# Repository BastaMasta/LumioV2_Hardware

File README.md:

# Lumio V2 Hardware

A repo containing all the hardware (shematic and PCB) files for the Lumio V2 Main Board

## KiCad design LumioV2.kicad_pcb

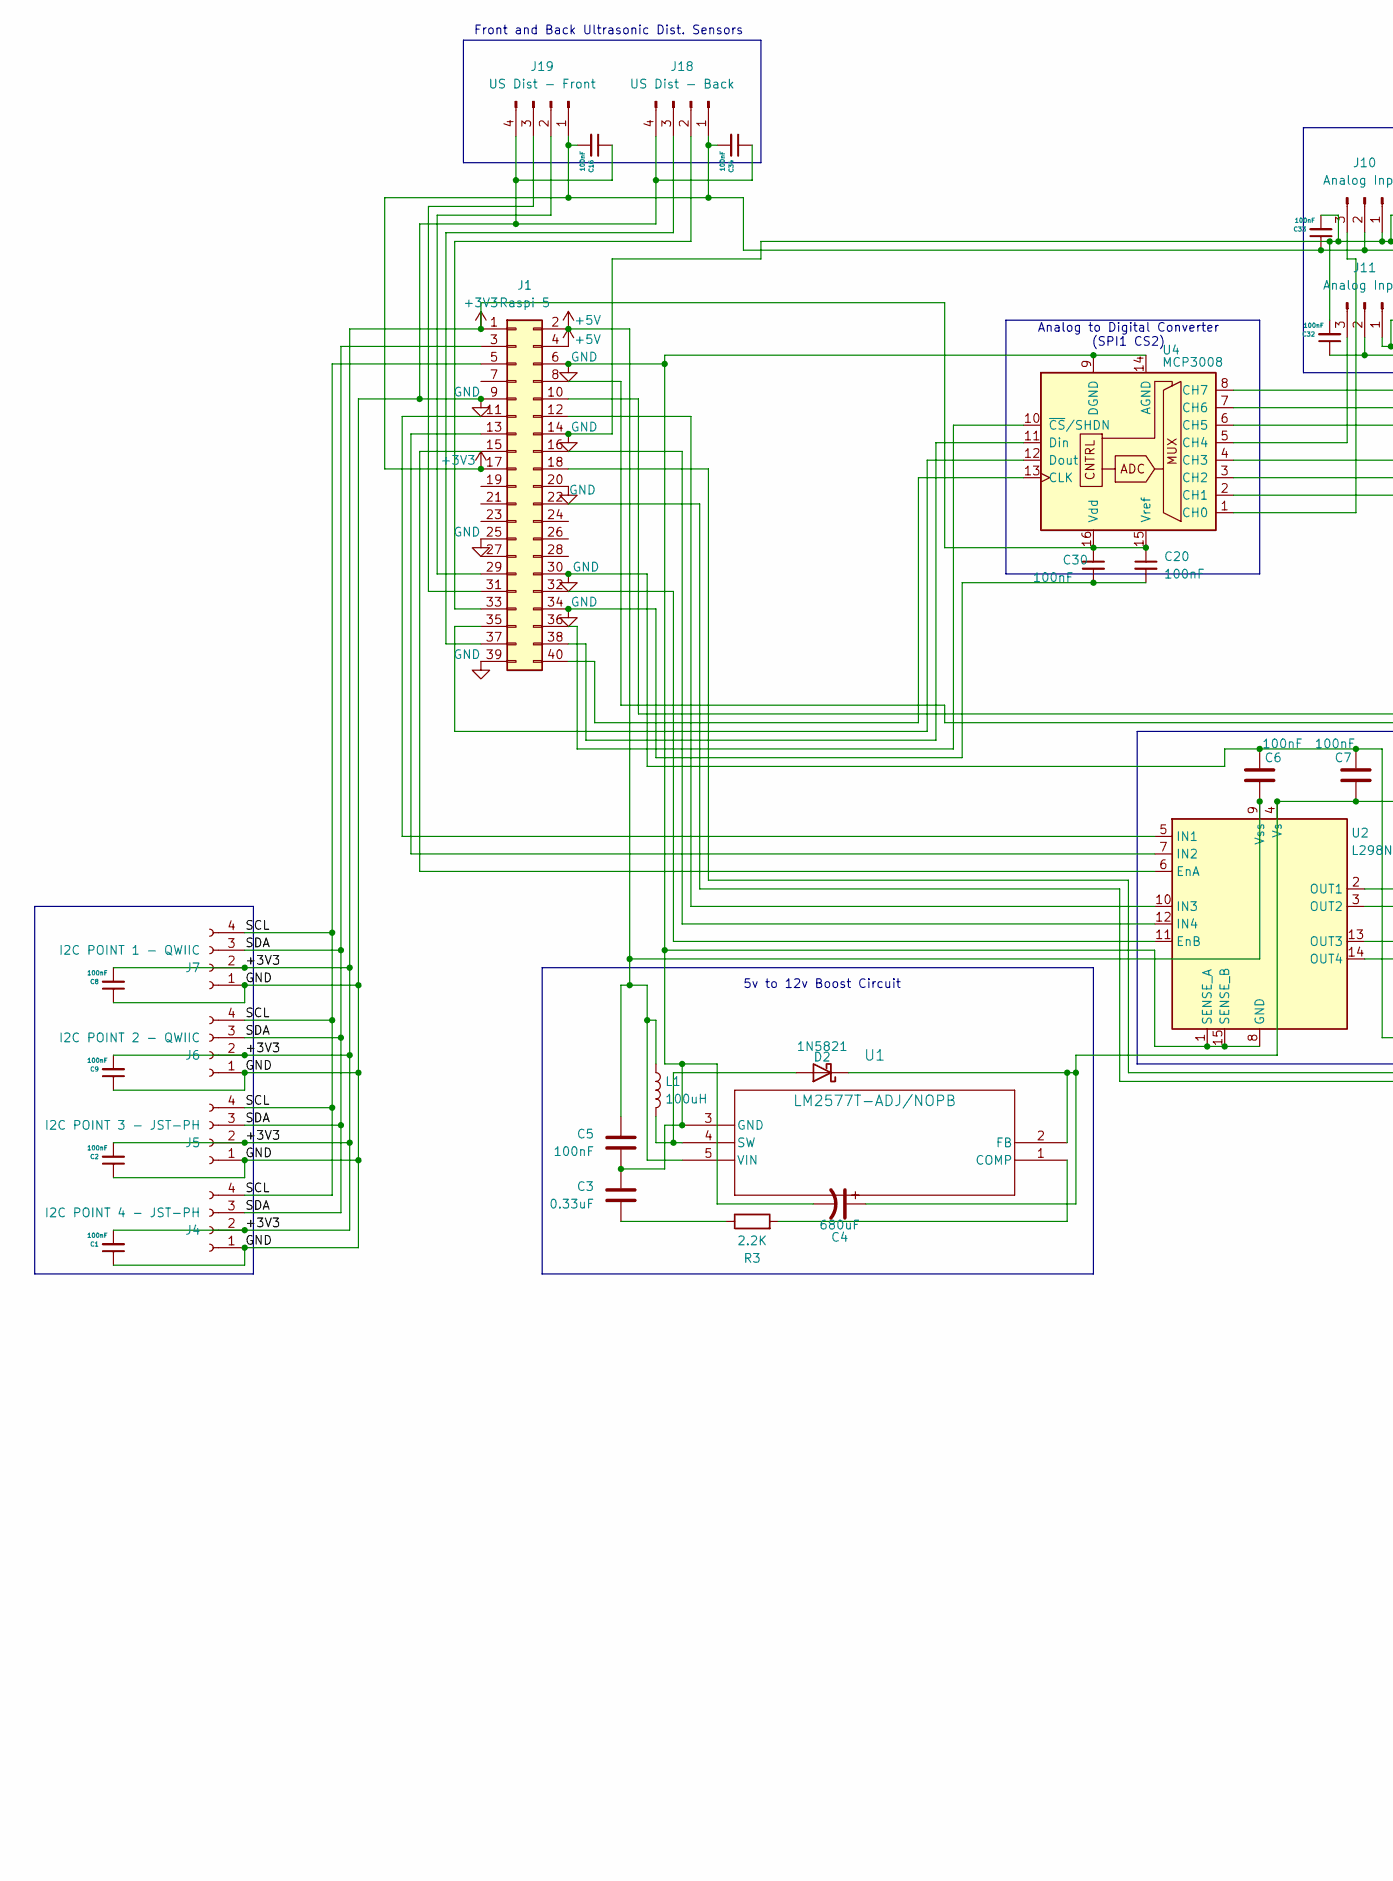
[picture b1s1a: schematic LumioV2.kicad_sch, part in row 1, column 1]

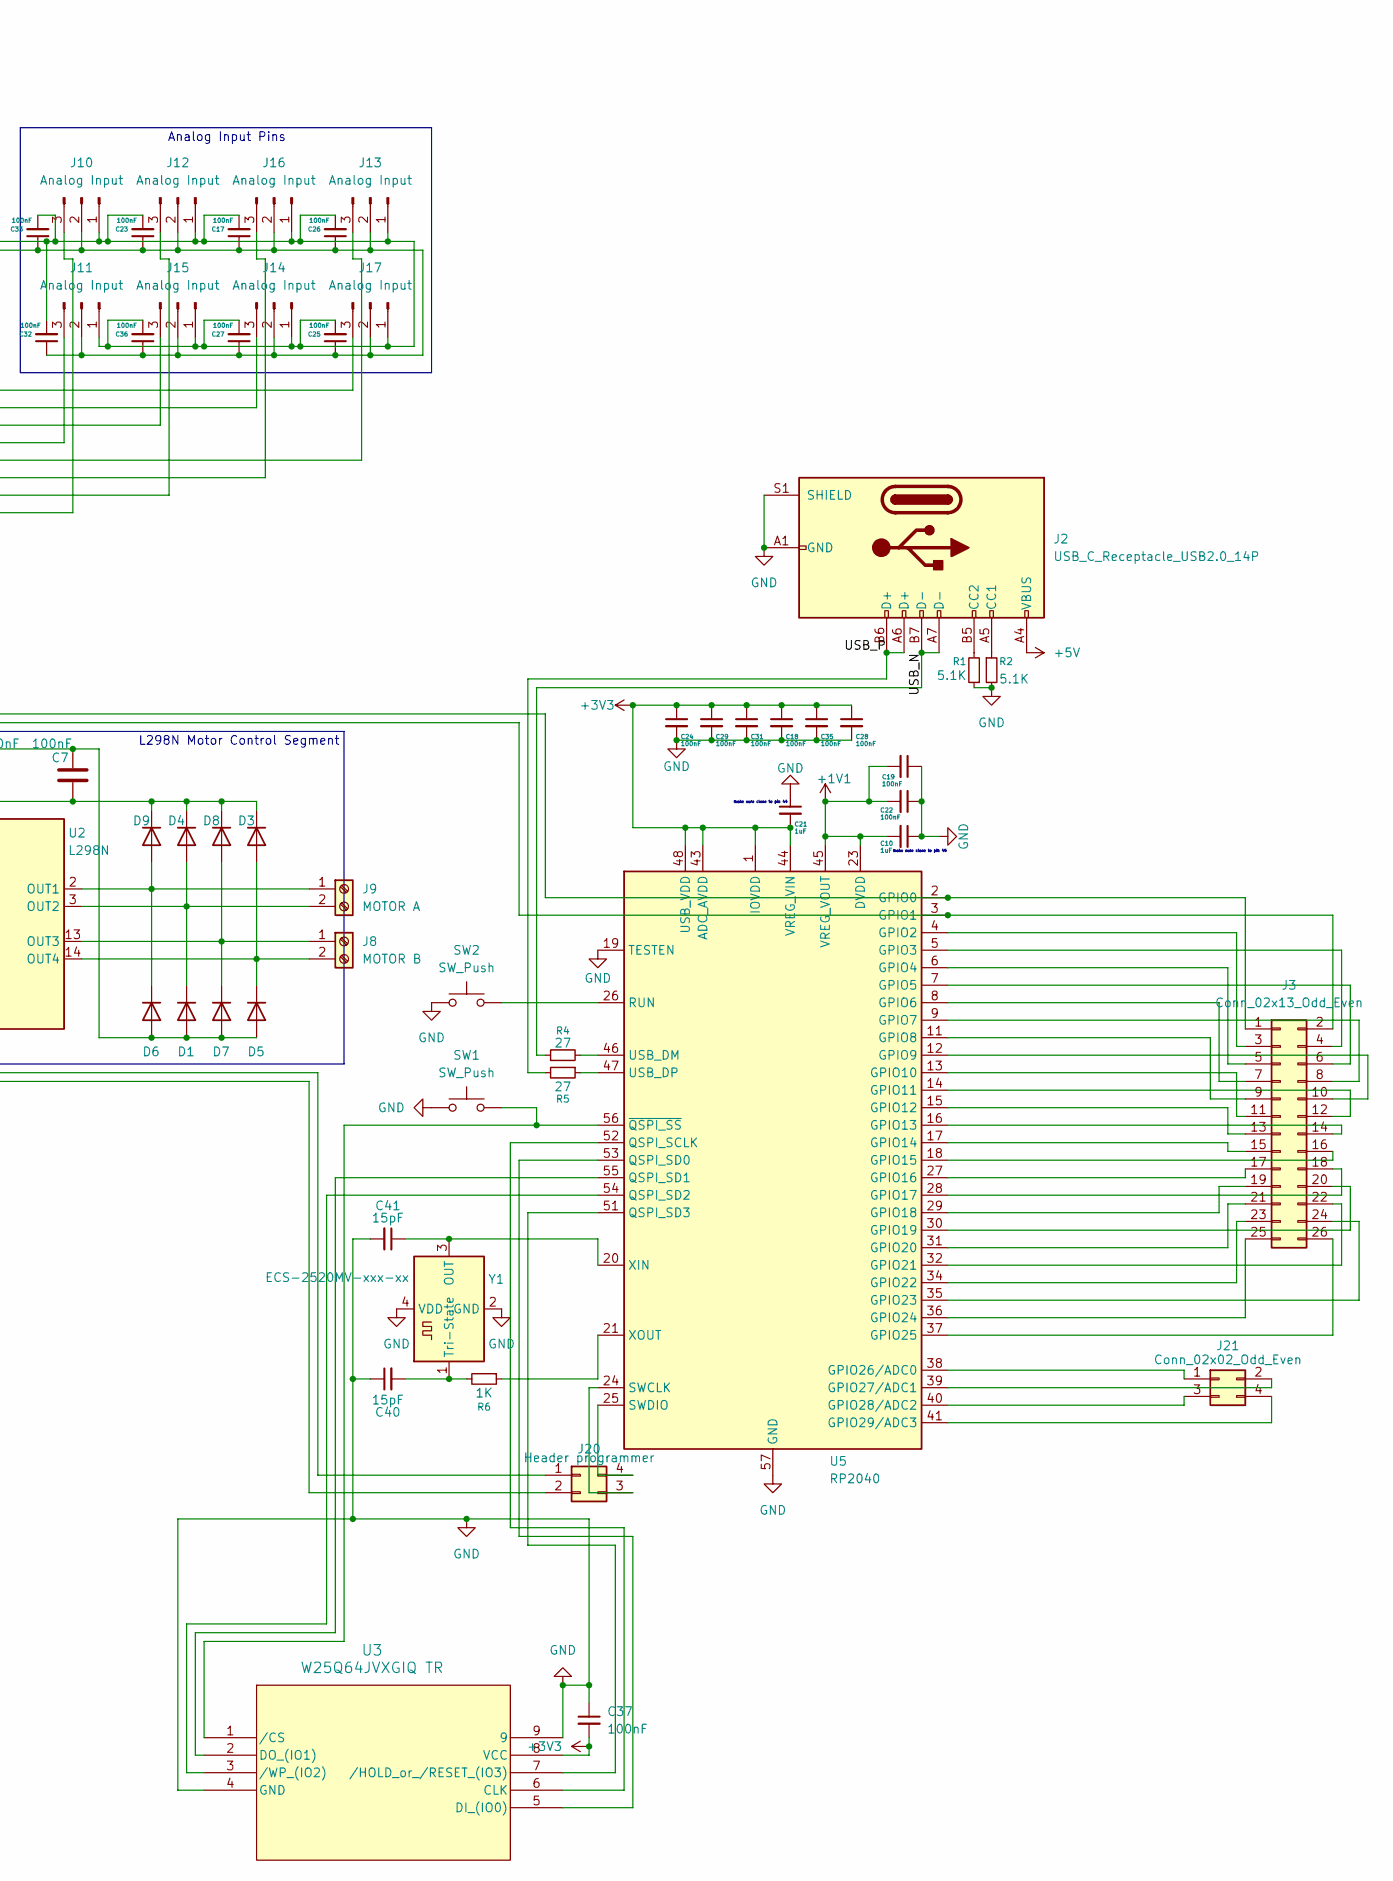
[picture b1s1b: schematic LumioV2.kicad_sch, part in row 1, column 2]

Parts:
C1, C2, C5, C6, C8, C9, C16, C17, C18, C19, C20, C22, C23, C24, C25, C26, C27, C28, C29, C30, C31, C32, C33, C34, C35, C36, C37: 100nF; C_0402_1005Metric_Pad0.74x0.62mm_HandSolder
C3: 0.33uF; C_0402_1005Metric_Pad0.74x0.62mm_HandSolder
C4: 680uF; CP_Elec_10x10
C7: 100nF; C_1210_3225Metric
C10, C21: 1uF; C_0402_1005Metric_Pad0.74x0.62mm_HandSolder
C40, C41: 15pF; C_0402_1005Metric_Pad0.74x0.62mm_HandSolder
D1, D3, D4, D5, D6, D7, D8, D9: SS34B; D_SMA_Handsoldering
D2: 1N5821; D_DO-201AD_P15.24mm_Horizontal
J1: Raspi 5; PinHeader_2x20_P2.54mm_Vertical; DIGIKEY ED-PI400EXT-G
J2: USB_C_Receptacle_USB2.0_14P; USB_C_Receptacle_G-Switch_GT-USB-7010ASV
J3: Conn_02x13_Odd_Even; PinHeader_2x13_P2.54mm_Horizontal
J4: I2C POINT 4 - JST-PH; JST_PH_B4B-PH-SM4-TB_1x04-1MP_P2.00mm_Vertical
J5: I2C POINT 3 - JST-PH; JST_PH_B4B-PH-SM4-TB_1x04-1MP_P2.00mm_Vertical
J6: I2C POINT 2 - QWIIC; JST_SH_BM04B-SRSS-TB_1x04-1MP_P1.00mm_Vertical
J7: I2C POINT 1 - QWIIC; JST_SH_BM04B-SRSS-TB_1x04-1MP_P1.00mm_Vertical
J8: MOTOR B; TerminalBlock_MaiXu_MX126-5.0-02P_1x02_P5.00mm
J9: MOTOR A; TerminalBlock_MaiXu_MX126-5.0-02P_1x02_P5.00mm
J10, J11, J12, J13, J14, J15, J16, J17: Analog Input; PinHeader_1x03_P2.54mm_Vertical
J18: US Dist - Back; PinHeader_1x04_P2.54mm_Vertical
J19: US Dist - Front; PinHeader_1x04_P2.54mm_Vertical
J20: Header programmer; PinHeader_2x02_P2.54mm_Vertical
J21: Conn_02x02_Odd_Even; PinHeader_2x02_P2.54mm_Vertical
L1: 100uH; L_Radial_D10.0mm_P5.00mm_Fastron_07M
R1, R2: 5.1K; R_0603_1608Metric
R3: 2.2K; R_0805_2012Metric_Pad1.20x1.40mm_HandSolder
R4, R5: 27; R_0603_1608Metric
R6: 1K; R_0603_1608Metric
SW1, SW2: SW_Push; SW_SPST_PTS647_Sx50
U1: LM2577T-ADJ/NOPB; T05A_TEX
U2: L298N; TO-220-15_P2.54x5.08mm_StaggerOdd_Lead4.58mm_Vertical
U3: W25Q64JVXGIQ TR; DFN-8-1EP_6x5mm_P1.27mm_EP4x4mm
U4: MCP3008; DIP-16_W7.62mm_Socket_LongPads; PART MCP3008-I/SL
U5: RP2040; QFN-56-1EP_7x7mm_P0.4mm_EP3.2x3.2mm
Y1: ECS-2520MV-xxx-xx; Oscillator_SMD_ECS_2520MV-xxx-xx-4Pin_2.5x2.0mm

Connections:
+1V1: C10.2, C19.2, C22.2, U5.23 (DVDD), U5.45 (VREG_VOUT), U5.50 (DVDD); also elsewhere on the board
+3V3: C1.2, C2.2, C8.2, C9.2, C16.2, C17.1, C18.1, C20.1, C21.2, C23.1, C24.1, C25.1, C26.1, C27.1, C28.1, C29.1, C30.1, C31.1, C32.1, C33.1, C34.2, C35.1, C36.1, C37.2, J1.1, J1.17 (3V3), J4.2, J5.2, J6.2, J7.2, J10.2, J11.2, J12.2, J13.2, J14.2, J15.2, J16.2, J17.2, J18.1, J19.1, U3.8 (VCC), U4.15 (Vref), U4.16 (Vdd), U5.1 (IOVDD), U5.10 (IOVDD), U5.22 (IOVDD), U5.33 (IOVDD), U5.42 (IOVDD), U5.43 (ADC_AVDD), U5.44 (VREG_VIN), U5.48 (USB_VDD), U5.49 (IOVDD); also elsewhere on the board
+5V: C5.1, C6.2, J1.2 (5V), J1.4 (5V), J2.A4 (VBUS), J2.A9 (VBUS), J2.B4 (VBUS), J2.B9 (VBUS), L1.1, U1.5 (VIN), U2.9 (Vss)
/SCL: J1.5, J4.4, J5.4, J6.4, J7.4
/SDA: J1.3 (SDA1), J4.3, J5.3, J6.3, J7.3
/USB_N: J2.A7 (D-), J2.B7 (D-), R4.1
/USB_P: J2.A6 (D+), J2.B6 (D+), R5.2
GND: C1.1, C2.1, C3.1, C4.2, C5.2, C6.1, C7.1, C8.1, C9.1, C10.1, C16.1, C17.2, C18.2, C19.1, C20.2, C21.1, C22.1, C23.2, C24.2, C25.2, C26.2, C27.2, C28.2, C29.2, C30.2, C31.2, C32.2, C33.2, C34.1, C35.2, C36.2, C37.1, C40.1, C41.2, D1.2 (A), D5.2 (A), D6.2 (A), D7.2 (A), J1.6 (GND), J1.9 (GND), J1.14 (GND), J1.20 (GND), J1.25 (GND), J1.30 (GND), J1.34 (GND), J1.39 (GND), J2.A1 (GND), J2.A12 (GND), J2.B1 (GND), J2.B12 (GND), J2.S1 (SHIELD), J4.1, J5.1, J6.1, J7.1, J10.1, J11.1, J12.1, J13.1, J14.1, J15.1, J16.1, J17.1, J18.4, J19.4, R1.1, R2.2, SW1.1, SW2.1, U1.3 (GND), U2.1 (SENSE_A), U2.8 (GND), U2.15 (SENSE_B), U3.4 (GND), U3.9, U4.9 (DGND), U4.14 (AGND), U5.19 (TESTEN), U5.57 (GND), Y1.2 (GND), Y1.4 (VDD); also elsewhere on the board
unnamed: C3.2, R3.1
unnamed: D1.1 (K), D4.2 (A), J9.2, U2.3 (OUT2)
unnamed: D2.2 (A), L1.2, U1.4 (SW)
unnamed: C4.1, C7.2, D2.1 (K), D3.1 (K), D4.1 (K), D8.1 (K), D9.1 (K), U1.2 (FB), U2.4 (Vs)
unnamed: D3.2 (A), D5.1 (K), J8.2, U2.14 (OUT4)
unnamed: D6.1 (K), D9.2 (A), J9.1, U2.2 (OUT1)
unnamed: D7.1 (K), D8.2 (A), J8.1, U2.13 (OUT3)
unnamed: J1.8, J3.2, U5.3 (GPIO1)
unnamed: J1.10, J3.1, U5.2 (GPIO0)
unnamed: J1.11, U2.5 (IN1)
unnamed: J1.12, U2.10 (IN3)
unnamed: J1.13, U2.7 (IN2)
unnamed: J1.15, U2.6 (EnA)
unnamed: J1.16, U2.12 (IN4)
unnamed: J1.18, J20.1
unnamed: J1.22, J20.2
unnamed: J1.29, J19.2
unnamed: J1.31, J19.3
unnamed: J1.32, U2.11 (EnB)
unnamed: J1.33, J18.2
unnamed: J1.35, U4.12 (Dout)
unnamed: J1.36, U4.10 (~CS/SHDN)
unnamed: J1.37, J18.3
unnamed: J1.38, U4.11 (Din)
unnamed: J1.40, U4.13 (CLK)
unnamed: J2.A5 (CC1), R2.1
unnamed: J2.B5 (CC2), R1.2
unnamed: J3.3, U5.4 (GPIO2)
unnamed: J3.4, U5.5 (GPIO3)
unnamed: J3.5, U5.6 (GPIO4)
unnamed: J3.6, U5.7 (GPIO5)
unnamed: J3.7, U5.8 (GPIO6)
unnamed: J3.8, U5.9 (GPIO7)
unnamed: J3.9, U5.11 (GPIO8)
unnamed: J3.10, U5.12 (GPIO9)
unnamed: J3.11, U5.13 (GPIO10)
unnamed: J3.12, U5.14 (GPIO11)
unnamed: J3.13, U5.15 (GPIO12)
unnamed: J3.14, U5.16 (GPIO13)
unnamed: J3.15, U5.17 (GPIO14)
unnamed: J3.16, U5.18 (GPIO15)
unnamed: J3.17, U5.27 (GPIO16)
unnamed: J3.18, U5.28 (GPIO17)
unnamed: J3.19, U5.29 (GPIO18)
unnamed: J3.20, U5.30 (GPIO19)
unnamed: J3.21, U5.31 (GPIO20)
unnamed: J3.22, U5.32 (GPIO21)
unnamed: J3.23, U5.34 (GPIO22)
unnamed: J3.24, U5.35 (GPIO23)
unnamed: J3.25, U5.36 (GPIO24)
unnamed: J3.26, U5.37 (GPIO25)
unnamed: J10.3, U4.1 (CH0)
unnamed: J11.3, U4.5 (CH4)
unnamed: J12.3, U4.2 (CH1)
unnamed: J13.3, U4.4 (CH3)
unnamed: J14.3, U4.7 (CH6)
unnamed: J15.3, U4.6 (CH5)
unnamed: J16.3, U4.3 (CH2)
unnamed: J17.3, U4.8 (CH7)
unnamed: J20.3, U5.24 (SWCLK)
unnamed: J20.4, U5.25 (SWDIO)
unnamed: J21.1, U5.38 (GPIO26/ADC0)
unnamed: J21.2, U5.39 (GPIO27/ADC1)
unnamed: J21.3, U5.40 (GPIO28/ADC2)
unnamed: J21.4, U5.41 (GPIO29/ADC3)
unnamed: R3.2, U1.1 (COMP)
unnamed: U3.6 (CLK), U5.52 (QSPI_SCLK)
unnamed: U3.5 (DI_(IO0)), U5.53 (QSPI_SD0)
unnamed: U3.2 (DO_(IO1)), U5.55 (QSPI_SD1)
unnamed: SW1.2, U3.1 (/CS), U5.56 (~QSPI_SS)
unnamed: U3.7 (/HOLD_or_/RESET_(IO3)), U5.51 (QSPI_SD3)
unnamed: U3.3 (/WP_(IO2)), U5.54 (QSPI_SD2)
unnamed: SW2.2, U5.26 (RUN)
unnamed: R4.2, U5.46 (USB_DM)
unnamed: R5.1, U5.47 (USB_DP)
unnamed: C41.1, U5.20 (XIN), Y1.3 (OUT)
unnamed: R6.1, U5.21 (XOUT)
unnamed: C40.2, R6.2, Y1.1 (Tri-State)

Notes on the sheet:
Analog to Digital Converter (SPI1 CS2)
5v to 12v Boost Circuit
make sure close to pin 45
make sure close to pin 44
Front and Back Ultrasonic Dist. Sensors
Analog Input Pins
L298N Motor Control Segment

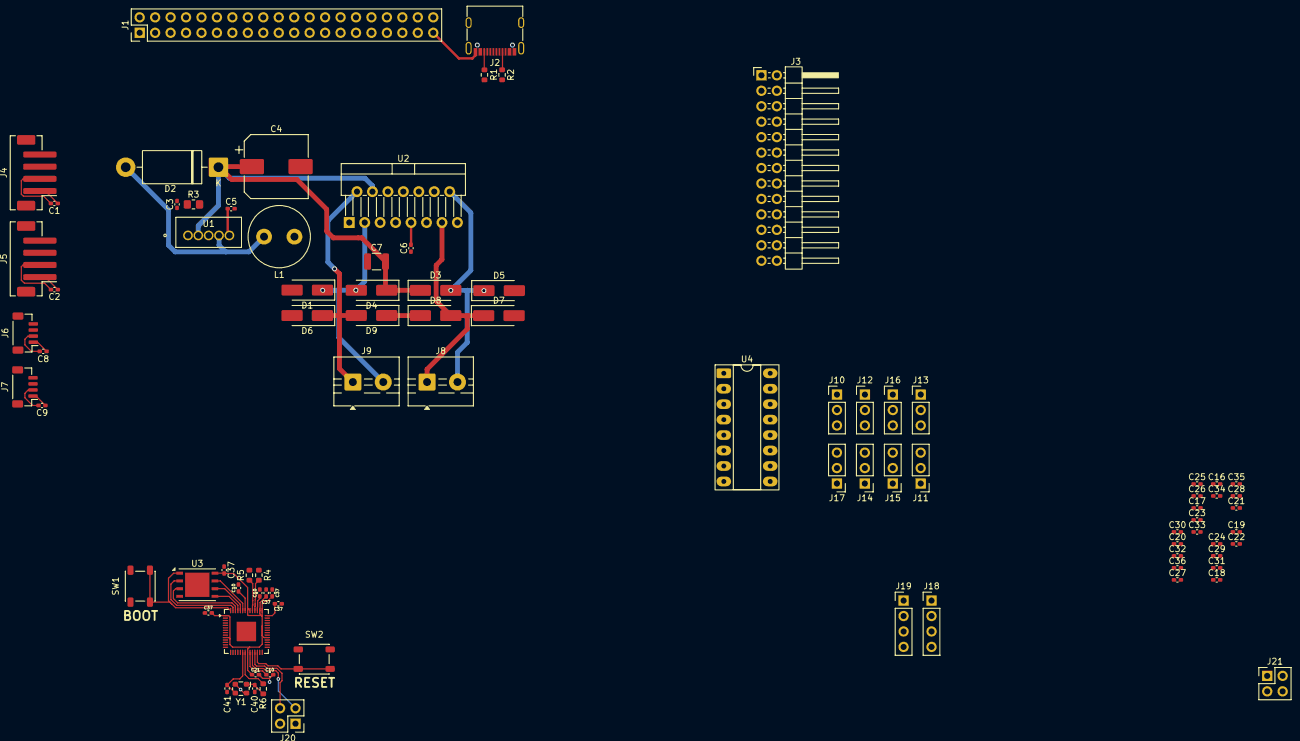
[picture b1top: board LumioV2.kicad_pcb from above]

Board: 2 copper layers, 86 parts (0 on the bottom side), 86 nets.

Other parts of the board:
C10#2, C10#3, C21#2: 1uF; C_0402_1005Metric_Pad0.74x0.62mm_HandSolder
C37#2, C37#3, C37#4, C37#5: 100nF; C_0402_1005Metric_Pad0.74x0.62mm_HandSolder

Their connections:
+1V1: C10#2.2, C10#3.2; also elsewhere on the board
+3V3: C21#2.2, C37#2.2, C37#3.2, C37#4.2, C37#5.2; also elsewhere on the board
GND: C10#2.1, C10#3.1, C21#2.1, C37#2.1, C37#3.1, C37#4.1, C37#5.1; also elsewhere on the board

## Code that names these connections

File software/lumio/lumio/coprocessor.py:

"""
lumio/coprocessor.py
--------------------
JSON-over-UART communication with the RP2040 co-processor.

Physical wiring (BCM GPIO numbering):
    RP2040 GPIO1  →  RPi5 GPIO15  (RXD / ttyAMA0)
    RP2040 GPIO2  →  RPi5 GPIO14  (TXD / ttyAMA0)

The RP2040 firmware speaks a simple newline-delimited JSON protocol:

  Host → RP2040   {"cmd": "gpio_write", "pin": 3, "value": 1}
  Host → RP2040   {"cmd": "gpio_read",  "pin": 4}
  Host → RP2040   {"cmd": "adc_read",   "pin": 26}   # GP26/27/28/29 only
  Host → RP2040   {"cmd": "gpio_set_mode", "pin": 5, "mode": "input", "label": "IR sensor"}
  Host → RP2040   {"cmd": "ping"}

  RP2040 → Host   {"ok": true,  "value": <int|float>}
  RP2040 → Host   {"ok": false, "error": "..."}
  RP2040 → Host   {"event": "sensor", "pin": 4, "value": 1}   (async push)
"""

import json
import logging
import threading
import time
from typing import Any, Callable

try:
    import serial
    SERIAL_AVAILABLE = True
except ImportError:
    SERIAL_AVAILABLE = False

from lumio.config import RP2040_UART_PORT, RP2040_UART_BAUD

log = logging.getLogger(__name__)


class RP2040:
    """
    Non-blocking UART interface to the RP2040 co-processor.

    A background reader thread pushes unsolicited 'event' frames to any
    registered callbacks; synchronous commands use a simple request-reply
    pattern with a configurable timeout.
    """

    def __init__(self, timeout: float = 1.0):
        self._timeout = timeout
        self._serial: serial.Serial | None = None
        self._lock = threading.Lock()
        self._reply_event = threading.Event()
        self._last_reply: dict | None = None
        self._event_callbacks: list[Callable[[dict], None]] = []
        self._running = False
        self._reader: threading.Thread | None = None
        self._connect()

    # ── Connection ────────────────────────────────────────────────────────────

    def _connect(self):
        if not SERIAL_AVAILABLE:
            log.warning("pyserial not available – RP2040 interface in stub mode")
            return
        try:
            self._serial = serial.Serial(
                RP2040_UART_PORT,
                RP2040_UART_BAUD,
                timeout=0.05,
            )
            self._running = True
            self._reader = threading.Thread(target=self._read_loop, daemon=True)
            self._reader.start()
            log.info("RP2040 UART open: %s @ %d baud", RP2040_UART_PORT, RP2040_UART_BAUD)
        except Exception as exc:
            log.error("Cannot open RP2040 UART: %s", exc)
            self._serial = None

    # ── Background reader ─────────────────────────────────────────────────────

    def _read_loop(self):
        buf = b""
        while self._running:
            try:
                chunk = self._serial.read(64)
                if chunk:
                    buf += chunk
                    while b"\n" in buf:
                        line, buf = buf.split(b"\n", 1)
                        self._dispatch(line.decode(errors="replace").strip())
            except Exception as exc:
                log.error("RP2040 read error: %s", exc)
                time.sleep(0.1)

    def _dispatch(self, line: str):
        if not line:
            return
        try:
            frame = json.loads(line)
        except json.JSONDecodeError:
            log.debug("RP2040 non-JSON: %r", line)
            return

        if "event" in frame:
            for cb in self._event_callbacks:
                try:
                    cb(frame)
                except Exception as exc:
                    log.error("Event callback error: %s", exc)
        else:
            # It's a reply to a synchronous command
            self._last_reply = frame
            self._reply_event.set()

    # ── Public API ────────────────────────────────────────────────────────────

    def on_event(self, callback: Callable[[dict], None]):
        """Register a callable that receives async event frames from RP2040."""
        self._event_callbacks.append(callback)

    def send(self, payload: dict) -> dict | None:
        """
        Send a JSON command and wait for a reply.
        Returns the reply dict, or None on timeout / connection error.
        """
        if self._serial is None:
            log.warning("RP2040 not connected – command dropped: %s", payload)
            return None
        with self._lock:
            self._reply_event.clear()
            self._last_reply = None
            try:
                line = json.dumps(payload) + "\n"
                self._serial.write(line.encode())
            except Exception as exc:
                log.error("RP2040 write error: %s", exc)
                return None
            if self._reply_event.wait(self._timeout):
                return self._last_reply
            log.warning("RP2040 reply timeout for: %s", payload)
            return None

    # ── Convenience wrappers ──────────────────────────────────────────────────

    def ping(self) -> bool:
        reply = self.send({"cmd": "ping"})
        return bool(reply and reply.get("ok"))

    def gpio_write(self, pin: int, value: int) -> bool:
        reply = self.send({"cmd": "gpio_write", "pin": pin, "value": value})
        return bool(reply and reply.get("ok"))

    def gpio_read(self, pin: int) -> int | None:
        reply = self.send({"cmd": "gpio_read", "pin": pin})
        if reply and reply.get("ok"):
            return reply.get("value")
        return None

    def gpio_set_mode(self, pin: int, mode: str, label: str = "") -> bool:
        """
        Configure a pin's mode on the RP2040.
        mode: 'input' | 'output' | 'adc' | 'pwm' | 'unused'
        ADC mode is only valid for GP26–GP29.
        """
        reply = self.send({"cmd": "gpio_set_mode", "pin": pin, "mode": mode, "label": label})
        return bool(reply and reply.get("ok"))

    def adc_read(self, pin: int) -> float | None:
        """Read ADC voltage (0.0–3.3 V) from an RP2040 ADC pin (GP26–GP29).
        Pin must already be configured in 'adc' mode via gpio_set_mode().
        """
        reply = self.send({"cmd": "adc_read", "pin": pin})  # firmware reads "pin", not "ch"
        if reply and reply.get("ok"):
            return reply.get("value")
        return None

    def close(self):
        self._running = False
        if self._serial:
            self._serial.close()
        log.info("RP2040 UART closed")

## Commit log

2026-03-28 deleted autosaves and removed cm5 footprint from pcb
2026-03-28 added README - primitive
2026-03-28 Routed display connector,
2026-03-28 Routed display connector, added MCP3008 ADC hooked up to spi1 cs2 for analog sensors, and added backup power capacitors to ensure the raspberry pi and the ups module dont die due to sudden surge
2026-03-30 added all footprints to schematics, also added all footprints to the pcb what's left: layout and routing
2026-03-31 Added rp2040 slave for extra gpios and current and voltage monitor
2026-04-04 smol changes
2026-04-04 began routing
2026-04-05 routed abit; replaced the MCP3008 footprint to a 16 pin socket, so that i can swap it easily if the user fries it somehow
2026-04-06 added few more step files
2026-04-07 updated to latest code
2026-04-08 resolved bugs, added documentation, and created filled zone for 3v3 on B.Cu and connected to 3v pins on raspi
2026-04-08 edited reports
2026-04-09 Add docs page and generated BOM
2026-04-09 added internship report
